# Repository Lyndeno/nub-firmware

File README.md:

# nub-firmware

Firmware for NUB(Nodal Hub), a long range mesh messaging system. Capstone Project for Electrical Engineering at the University of Alberta.

## Frame Format

### NUB to NUB

| TAG | Message Type | Size of Path | Path | Data Size | Data |
| --- | ------------ | ------------ | ---- | --------- | ---- |
| ```0x02``` | 1 Byte | 1 Byte | Variable | 2 Bytes | ```Data Size``` Bytes |

### Passing through ATmega

| TAG | Data Len | Message Type | Data Size | Data |
| --- | ------------ | ------------ | ---- | --------- |
| ```0x02``` | 1 Byte | 1 Byte | 2 Bytes | ```Data Size``` bytes |

### Message Types

| Message Type Byte | Message |
| ------- | ----------------- |
| 0x01 | Text Messages |
| 0x02 | Connected/Disconnected phone |
| 0x03 | Adjust NUB Mesh |
| 0x04 | Message Acknowledgement |

## To-Do

- [x] Access point (mostly done)
- [x] Communications with Android app
- [x] UART communication between MCU and ESP8266
- [x] UART communication between MCU and transceiver
- [ ] ~~Power management (Sleep, power button)~~ batteries not allowed for project anymore
- [ ] Status LEDs
- [ ] Serial output? (For debugging)

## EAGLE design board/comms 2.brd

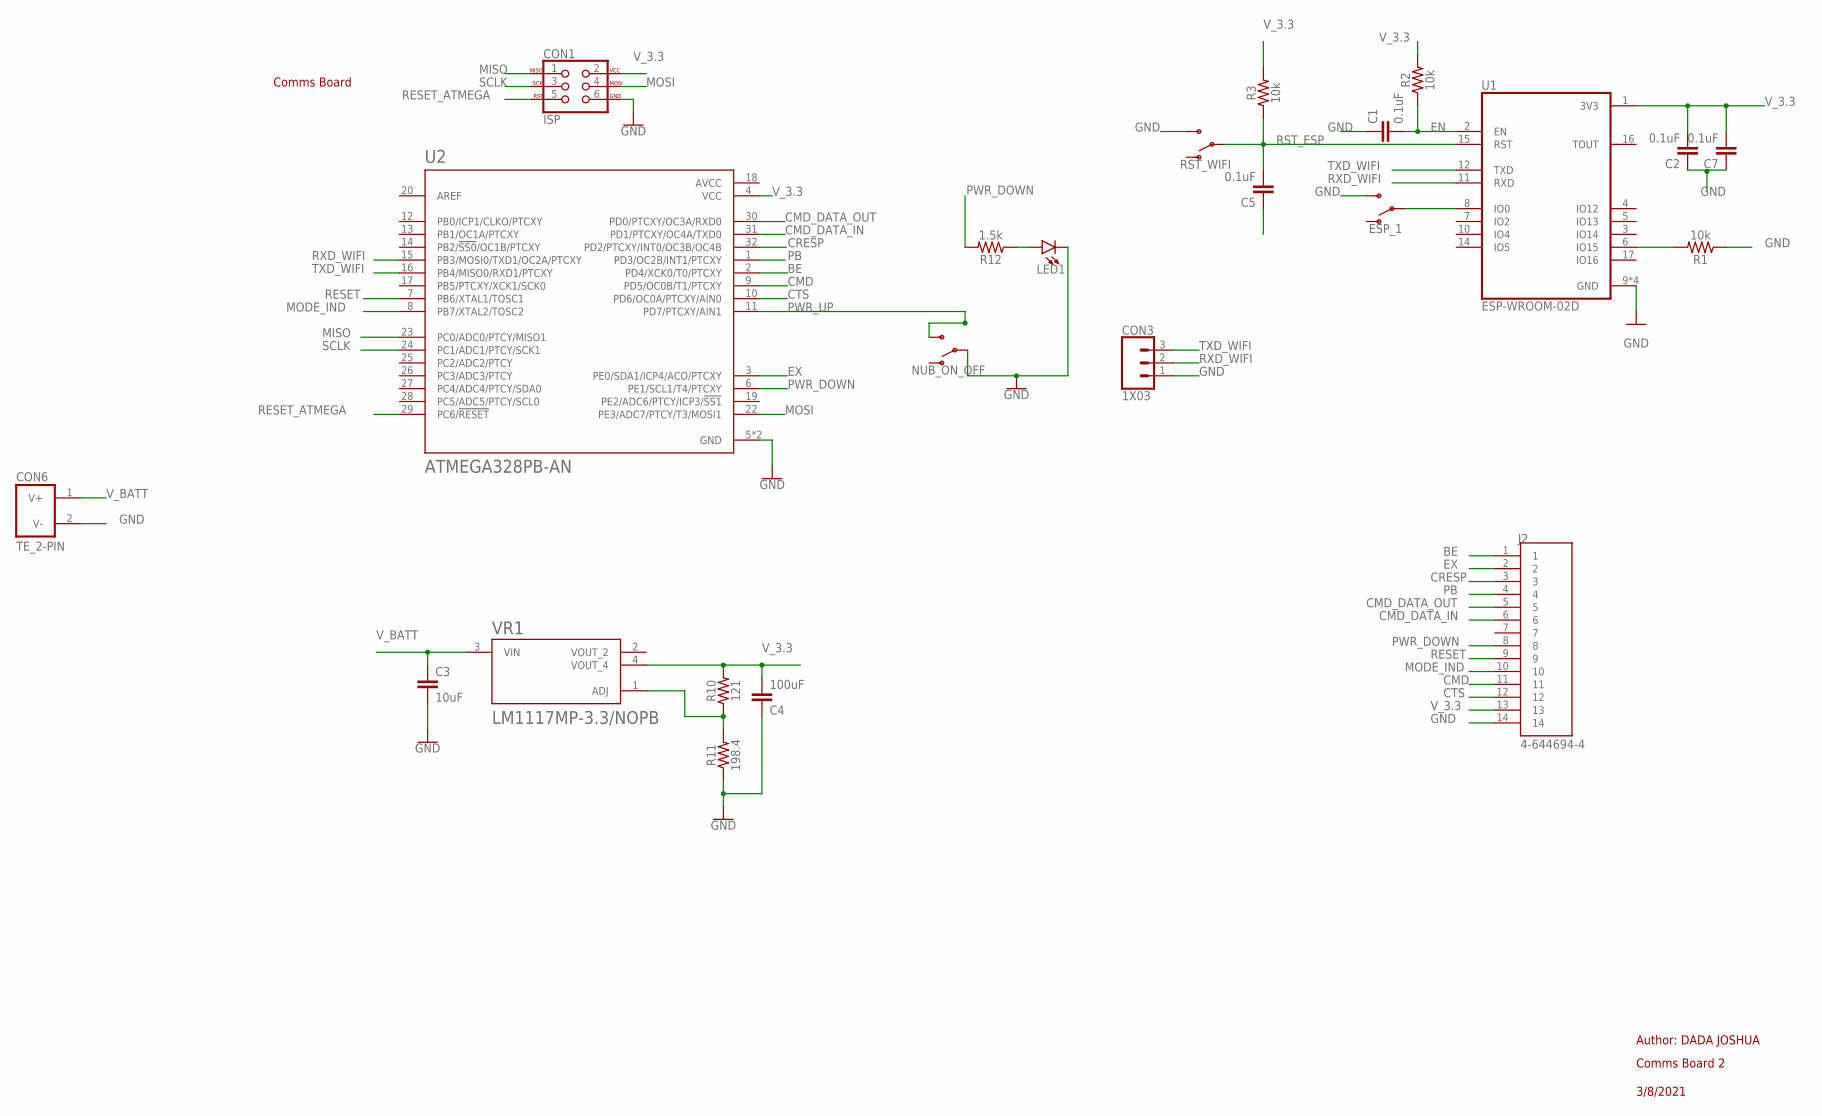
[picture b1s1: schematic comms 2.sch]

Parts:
C1, C2, C5, C7: 0.1uF; 1210
C3: 10uF; 1210
C4: 100uF; 1210
CON1: ISP; ISP_CONNECTOR
CON3: 1X03
CON6: TE_2-PIN
ESP_1: SWITCH_SPDT
J2: 4-644694-4; TE_4-644694-4
LED1: LED_THROUGH-HOLE
NUB_ON_OFF: SWITCH_SPDT
R1, R2, R3: 10k; 1210
R10: 121; 1210
R11: 198.4; 1210
R12: 1.5k; 1210
RST_WIFI: SWITCH_SPDT
U1: ESP-WROOM-02D; MODULE_ESP-WROOM-02D
U2: ATMEGA328PB-AN; QFP80P900X900X120-32N
VR1: LM1117MP-3.3/NOPB; VREG_LM1117MP-3.3/NOPB

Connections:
AVCC: U2.18 (AVCC)
BE: J2.1, U2.2 (PD4/XCK0/T0/PTCXY)
CMD: J2.11, U2.9 (PD5/OC0B/T1/PTCXY)
CMD_DATA_IN: J2.6, U2.31 (PD1/PTCXY/OC4A/TXD0)
CMD_DATA_OUT: J2.5, U2.30 (PD0/PTCXY/OC3A/RXD0)
CRESP: J2.3, U2.32 (PD2/PTCXY/INT0/OC3B/OC4B)
CTS: J2.12, U2.10 (PD6/OC0A/PTCXY/AIN0)
EN: C1.2, R2.1, U1.2 (EN)
EX: J2.2, U2.3 (PE0/SDA1/ICP4/ACO/PTCXY)
GND: C1.1, C2.1, C3.2, C4.1, C5.1, C7.1, CON1.6, CON3.1, CON6.2 (V-), ESP_1.3 (S), J2.14, LED1.C, NUB_ON_OFF.2, R1.1, R11.1, RST_WIFI.3 (S), U1.9 (GND), U1.13 (GND), U1.18 (GND), U1.19 (GND), U2.5 (GND), U2.21 (GND)
MISO: CON1.1, U2.23 (PC0/ADC0/PTCY/MISO1)
MODE_IND: J2.10, U2.8 (PB7/XTAL2/TOSC2)
MOSI: CON1.4, U2.22 (PE3/ADC7/PTCY/T3/MOSI1)
unnamed: R10.1, R11.2, VR1.1 (ADJ)
unnamed: R1.2, U1.6 (IO15)
unnamed: LED1.A, R12.1
unnamed: ESP_1.2, U1.8 (IO0)
PB: J2.4, U2.1 (PD3/OC2B/INT1/PTCXY)
PWR_DOWN: J2.8, R12.2, U2.6 (PE1/SCL1/T4/PTCXY)
PWR_UP: NUB_ON_OFF.3 (S), U2.11 (PD7/PTCXY/AIN1)
RESET: J2.9, U2.7 (PB6/XTAL1/TOSC1)
RESET_ATMEGA: CON1.5, U2.29 (PC6/!RESET)
RST_ESP: C5.2, R3.1, RST_WIFI.2, U1.15 (RST)
RXD_WIFI: CON3.2, U1.11 (RXD), U2.15 (PB3/MOSI0/TXD1/OC2A/PTCXY)
SCLK: CON1.3, U2.24 (PC1/ADC1/PTCY/SCK1)
TXD_WIFI: CON3.3, U1.12 (TXD), U2.16 (PB4/MISO0/RXD1/PTCXY)
V_3.3: C2.2, C4.2, C7.2, CON1.2, J2.13, R2.2, R3.2, R10.2, U1.1 (3V3), U2.4 (VCC), VR1.4 (VOUT_4)
V_BATT: C3.1, CON6.1 (V+), VR1.3 (VIN)

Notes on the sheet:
Comms Board
Author: DADA JOSHUA
Comms Board 2
3/8/2021

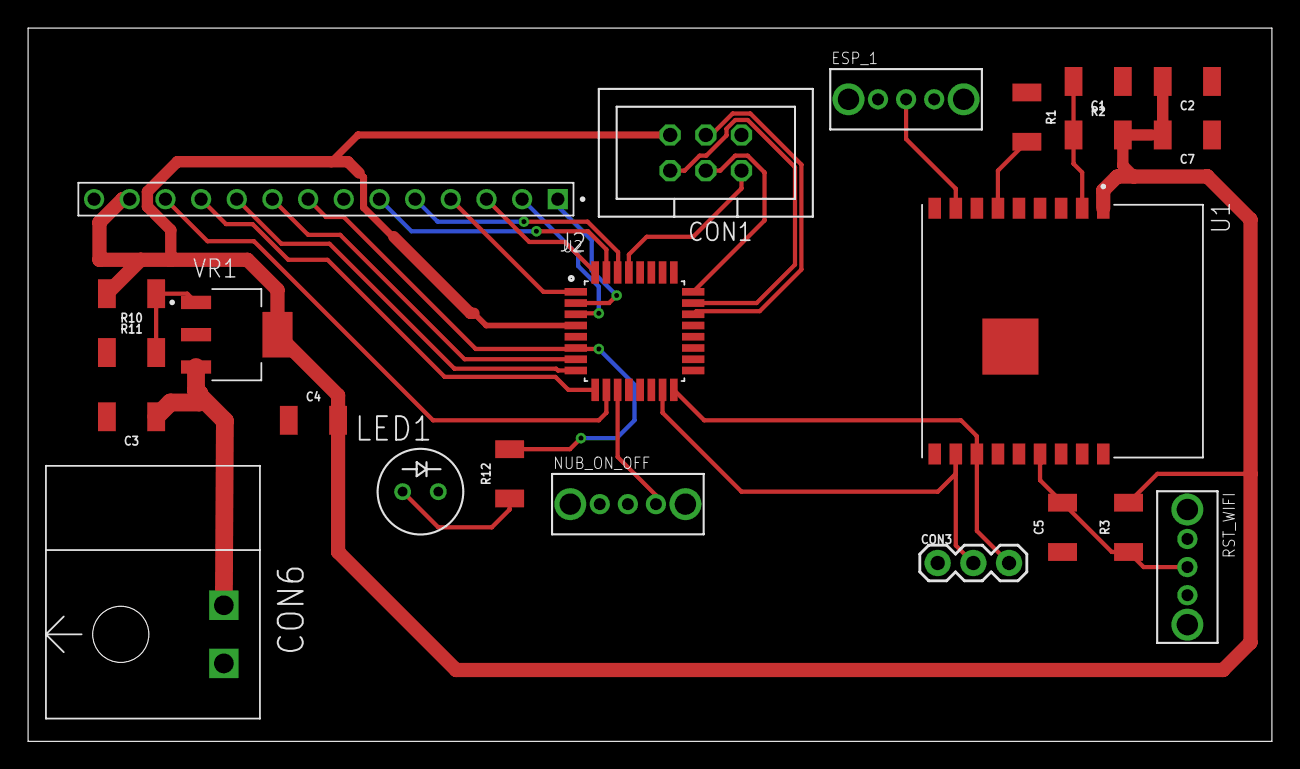
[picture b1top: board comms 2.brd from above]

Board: 2 copper layers, 88.6 x 50.8 mm, 23 parts (0 on the bottom side), 27 nets.

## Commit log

2021-01-15 Created folder structure
2021-01-15 Added more files for future use
2021-01-15 Updated individual device READMEs
2021-01-15 Updated spelling
2021-01-15 Initial Code for access point mode
2021-01-15 Added reference link
2021-01-15 Add todos for code work
2021-01-15 Add todo list to main readme
2021-01-15 Fix To-DO
2021-01-23 Ignore vscode compiler config
2021-01-23 MCU: Initial Code
2021-01-25 Add code for turning off usart power reduction
2021-01-25 Add vscode compiler settings
2021-01-29 Create a shell of each function and comment on what they do
2021-02-04 Add UART receive code
2021-02-04 Add simple if statement to routing function
2021-02-04 Add ideas and todo to main
2021-02-09 Define address and message lengths
2021-02-09 Advance code for receiving from wifi
2021-02-09 Tweak other transmission code
2021-02-15 Ignore vscode arduino config
2021-02-15 Housekeeping
2021-02-15 Add vscode workspace
2021-02-15 Setup mplabx project
2021-02-15 Setup WiFi toolchain
2021-02-15 Add led blink code to test on-board xplained debugger
2021-02-15 Updated configuration
2021-02-15 Update ignored files
2021-02-15 Define cpu speed before util/delay.h
2021-02-16 Listen on port 80 for bytes for testing
2021-02-16 Define UART registers
2021-02-16 Add io.h to mplab
2021-02-20 Blink more lights for breadboard testing
2021-02-20 More settings for arduino ide
2021-02-20 Remove barebones 'Ardruino' ESP code
2021-02-20 Add ESP8266 RTOS-SDK hello-world example
2021-02-20 Add rest of ESP8266 RTOS-SDK hello-world example
2021-02-20 Adjust vscode c_cpp settings to include RTOS SDK
2021-02-20 Fix up intellisense options
2021-02-20 Reference ESP SDK and Compiler with ENV vars
2021-02-20 Add ___ESP_FILE___ to cpp defines
2021-02-20 Initial code for access point
2021-02-20 Rename files
2021-02-22 Don't prompt cmake config on vscode launch
2021-02-22 Do not prompt for cmake config vscode
2021-02-23 Test MCU uart output to computer
2021-02-23 Initial RTOS SDK UART output
2021-02-24 Use debugWIRE
2021-02-24 Initial circular buffer for UART reception
2021-02-24 Disable debugWIRE
2021-02-24 Organize the code somewhat
2021-02-24 Updated READMEs
2021-02-26 Updated XC8 toolchain through package manager
2021-03-03 Changed clock speed to 8MHz, Baud to 19200 or 57600
    Potentially need to play around with clock speed if want to get 115200bps working
2021-03-10 Trying to get data transfer to work without any delay
2021-03-10 changed esp baud
2021-03-10 Create buffer struct to make code more reusable
2021-03-11 Finally got no delay UART reading working
2021-03-11 Optimize message handler
2021-03-11 further optimization
2021-03-11 Fix buffer initialization to not refer to global buffer
2021-03-11 Switch to redfined registers and create a simple TX function for WiFi UART
2021-03-11 Rename buffer0 to WiFi RX buffer
2021-03-11 Move frame logic to function for re-use
2021-03-11 Added skeleton for other messgae types
2021-03-11 Clean up garbage comments
2021-03-11 Add transceiver registers
2021-03-11 Use define for interrupt vector
2021-03-11 Interrupt prototype is unnecessary
2021-03-11 Define tranceiver interrupt vector
2021-03-11 Add formatted documentation and comments. Rename the UART init function to indicate its use for WiFi.
2021-03-11 Add size parameter to buffer init and rename max to size in struct
2021-03-11 Put CPU and BAUD settings into proper headers
2021-03-11 Move message routing to own source files
2021-03-11 Rename routing functions
2021-03-11 Organize ESP code for further work
2021-03-11 MPlab configuration changes
2021-03-11 Add board schematics
2021-03-11 Added frame data tables
2021-03-11 Add design goals for the ATmega programming
2021-03-15 Remove unnecessary station code
2021-03-15 Initial UDP server code. Receives and repeats back packets
2021-03-15 WiFi reason variable not needed for AP mode
2021-03-15 WiFi event group not needed
2021-03-15 Some comments
2021-03-18 Define queues and frame type for message routing
2021-03-18 Initialize uart queue
2021-03-18 Initial byte to struct conversion task
2021-03-19 Add functions to read and write to uart queue, for readability
2021-03-19 Create function for converting messages to bytestream for uart
2021-03-19 Turn for loops into while loops for consistency
2021-03-19 Do not need UART event queue at this time
2021-03-19 Define queuehandles
2021-03-19 Fix for loop index definition
2021-03-19 Correct queue definitions to uart and not wifi
2021-03-19 Define UART RX and TX traffic tasks
2021-03-27 Add ip address to frame data
2021-03-27 Separate udp receive into own taks in prep for separate transmit task
2021-03-28 Use UART for debug temporarily
2021-03-28 Define headers only once
2021-03-28 Split UDP server into tasks
2021-03-28 Disable uart for debugging purposes
2021-03-29 Define simple structure for storing connected device information
2021-03-29 Move definition of max wifi devices to header for accessibility
2021-03-29 Rename routing tasks to be more accurate
2021-03-29 Define a struct for our wifi table
2021-03-29 Move message handling into own function so task can perform different actions for different message types
2021-03-30 Initial code for handling the connected device table
2021-03-30 Remove "default" switch cases
2021-03-30 Initial code to queue up device removal on WiFi disconnect
2021-03-30 Free contents of state change mac
2021-04-02 Handle device frames that handle connect/disconnect
2021-04-02 Handle connection frame in its own function
2021-04-02 Add function prototype for connection frame function
2021-04-02 Add variable names to prototypes for clarity
2021-04-02 Add a little todo
2021-04-02 launch uart tasks in init
2021-04-02 Use max delay for uart
2021-04-02 Add task prototypes for comms
2021-04-02 Add routing task prototypes
2021-04-02 Create udp init function
2021-04-02 Remove blank lines
2021-04-02 Configure for message routing
2021-04-02 Message routing from network to UART works
2021-04-02 Change UART TX to use variable-size structures instead of single bytes
2021-04-02 Clean up byte handling function
2021-04-04 Stuff
2021-04-04 Fix mac index in uart message
2021-04-04 Remove temporary testing code
2021-04-05 Add header function/task comment blocks
2021-04-06 Update to-do list
2021-04-07 Transceiver/ MCU code
2021-04-07 Move app to main branch
2021-04-07 ignore vcs
2021-04-07 Fix esp adding wifi message type to uart when not needed
2021-04-08 Correct the message length variable sent over uart
2021-04-08 Add kyle main stuff
2021-04-08 Add transceiver code
2021-04-08 Rename UART setup function to something generic
2021-04-08 Define more UART vars
2021-04-08 UART header
2021-04-08 Remove led flash from isr
2021-04-08 Initial groundwork for transceiver uart
2021-04-08 Add function to comms header
2021-04-08 Transfer over some buffer functions
2021-04-08 Move buffer init into uart setup and setup transceiver rx buffer
2021-04-08 Apply Eri's work
2021-04-08 Create enum to identify uart ports
2021-04-08 TXwrite now takes enum to specify device
2021-04-08 Switch order of enum for compatibility with older code
2021-04-08 Change transceiver setup to use TXwrite with enum
2021-04-08 Update message.c with new TXwrite calls
2021-04-08 Messaging udp protocol
2021-04-08 Manually assign enum values for clarity
2021-04-08 Adjjust getchar to use buffer structures
2021-04-08 skipbuffer now uses buffer structure
2021-04-08 parse buffer functions use structure
2021-04-08 peekchar uses structure buffers
2021-04-08 message.c calls char with enum
2021-04-08 Fix protoypes
2021-04-08 Fix skipbuffer call
2021-04-08 Fix buffer references
2021-04-08 getChar updates inside of transceiver setup
2021-04-08 Formatting
2021-04-08 ESP now notifies MCU of connection changes
2021-04-08 remove unnecessary definitions from messaging.c
2021-04-08 Remove definitions from main
2021-04-08 Remove definitions from comms
2021-04-08 Start organizing definitions
2021-04-08 Update mplab configuration
2021-04-08 More mplab stuff
2021-04-08 Messages are passing throug the atmega and esp
2021-04-08 Receiving messages back on the phone
2021-04-08 Updated App Layout
2021-04-08 Do not overwrite whole connection table
2021-04-09 Programmed Disconnect Button to disconnect from the Wifi and return back to Connect page
2021-04-09 Testing raw bytes
2021-04-09 Fix attempt on Connect/Disconnect Button to disconnect from the Wifi and return back to Connect page
2021-04-10 Checked off mcu-esp comms
2021-04-10 Updated MCU readme
2021-04-10 Add function to check if device exists in table
2021-04-11 Send message directly to local WiFi device instead of NUB network
2021-04-11 Updated network sharing
    Updated network connection, one unit can now broadcast and have the other until at it to its network list and send it to the first unit for it to have.
    Still some bugs in the code and things to clean up though.
2021-04-11 Added in input from esp UART
    Able to take ESP messages on UART1 and search the NUB for which NUB that phone is connected to and send out that DSN address which will be used for sending messages.
2021-04-12 Attempted a new MAC Address retrieval in MainActivity
2021-04-12 debug crashing
2021-04-12 Implemented hex to byte conversion for mac address
2021-04-13 Remove address operator on a pointer
2021-04-13 Move socket to global variable
2021-04-13 Sync working
    Added stuff to main and messages
2021-04-13 Swap UART ports
2021-04-13 Copied main over
2021-04-13 Moved rest of main over
2021-04-13 Copy messaging files over
2021-04-13 Transfer stuff
2021-04-13 Mplab config
2021-04-13 When send button is pressed, check if ESP has been notified of presence and if not then notify ESP
2021-04-13 Set notified flag to true when ESP is notified
2021-04-13 Variable packet length
2021-04-13 Move packet reception to own thread so messages can be received all the time
2021-04-13 Trim output to remove MAC bytes from string
2021-04-13 Show mac address of sender when receiving messages
2021-04-13 last minute
2021-04-14 Update readme checklist
2021-04-17 Update board files
2021-04-18 Added antenna schematic

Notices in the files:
parts and their libraries:
SparkFun-PowerSymbols: Licensing: Creative Commons ShareAlike 4.0 International - https://creativecommons.org/licenses/by-sa/4.0
